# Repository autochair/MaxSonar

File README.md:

# MaxSonar
Board design and code for communication with Maxbotix MaxSonar sensors

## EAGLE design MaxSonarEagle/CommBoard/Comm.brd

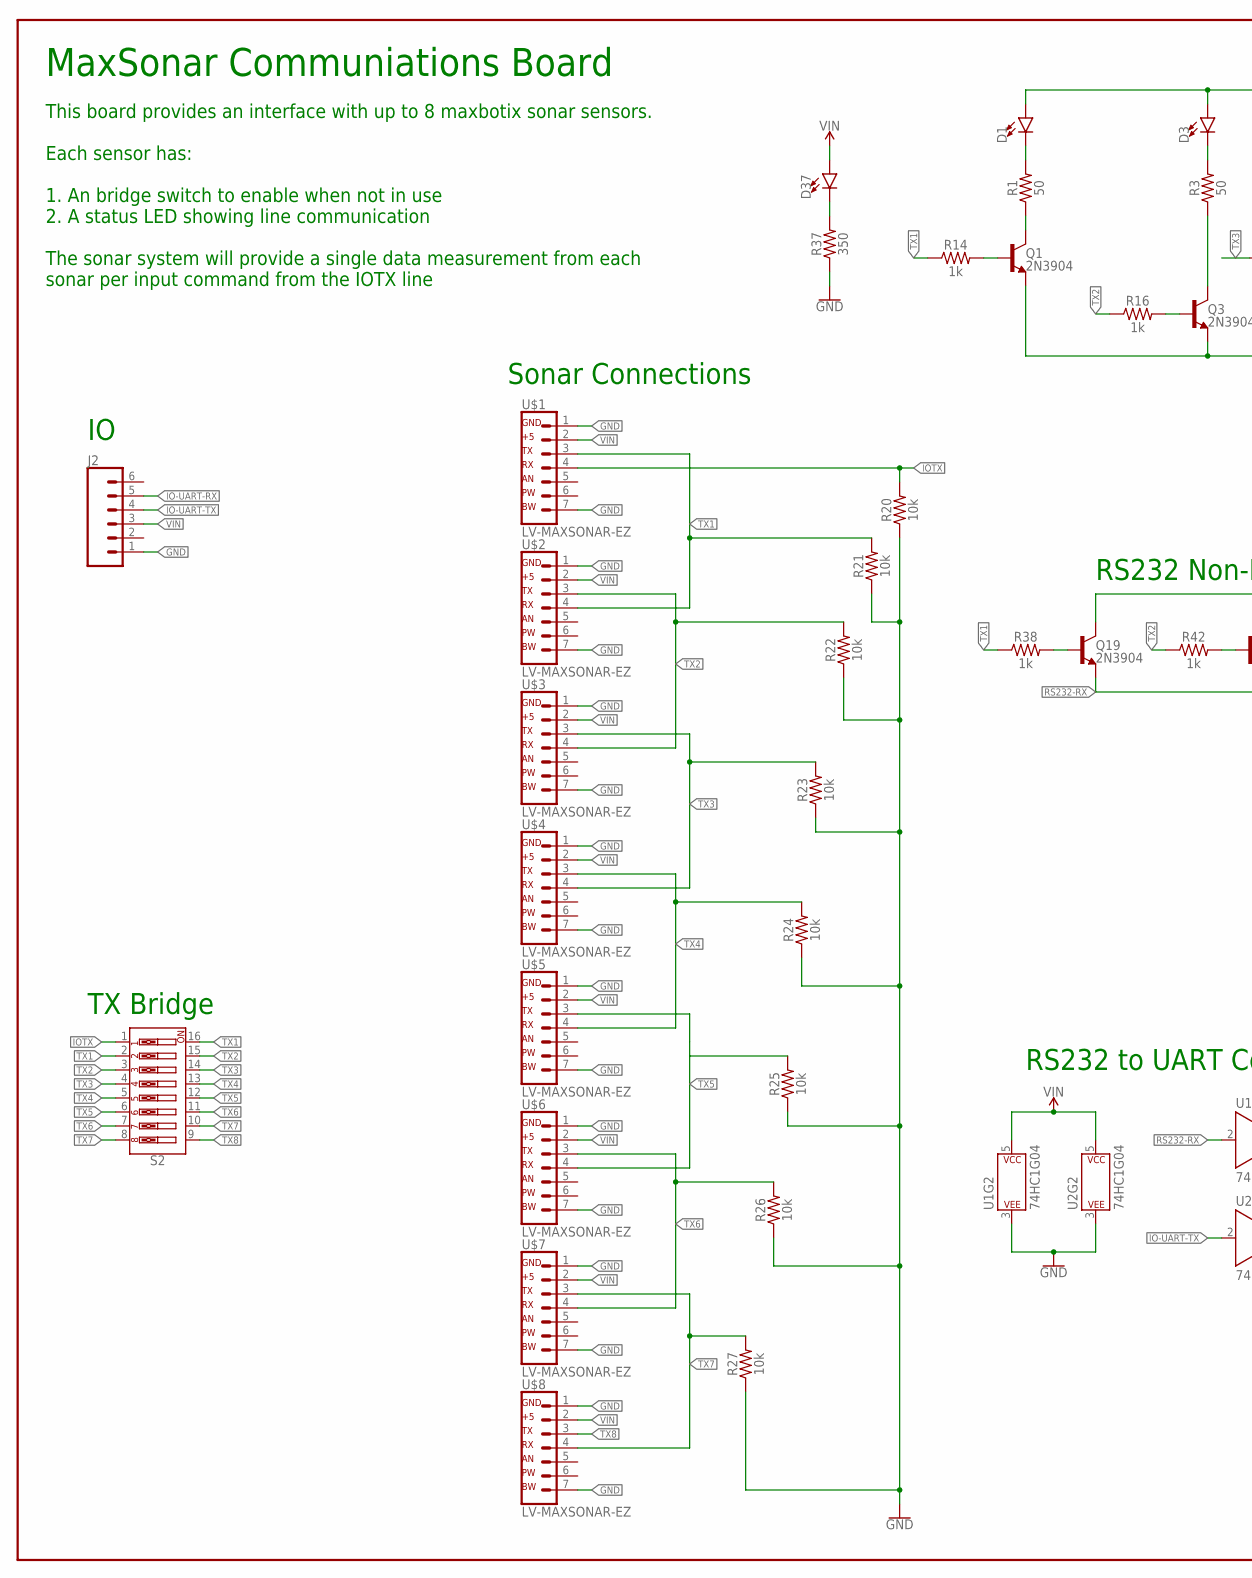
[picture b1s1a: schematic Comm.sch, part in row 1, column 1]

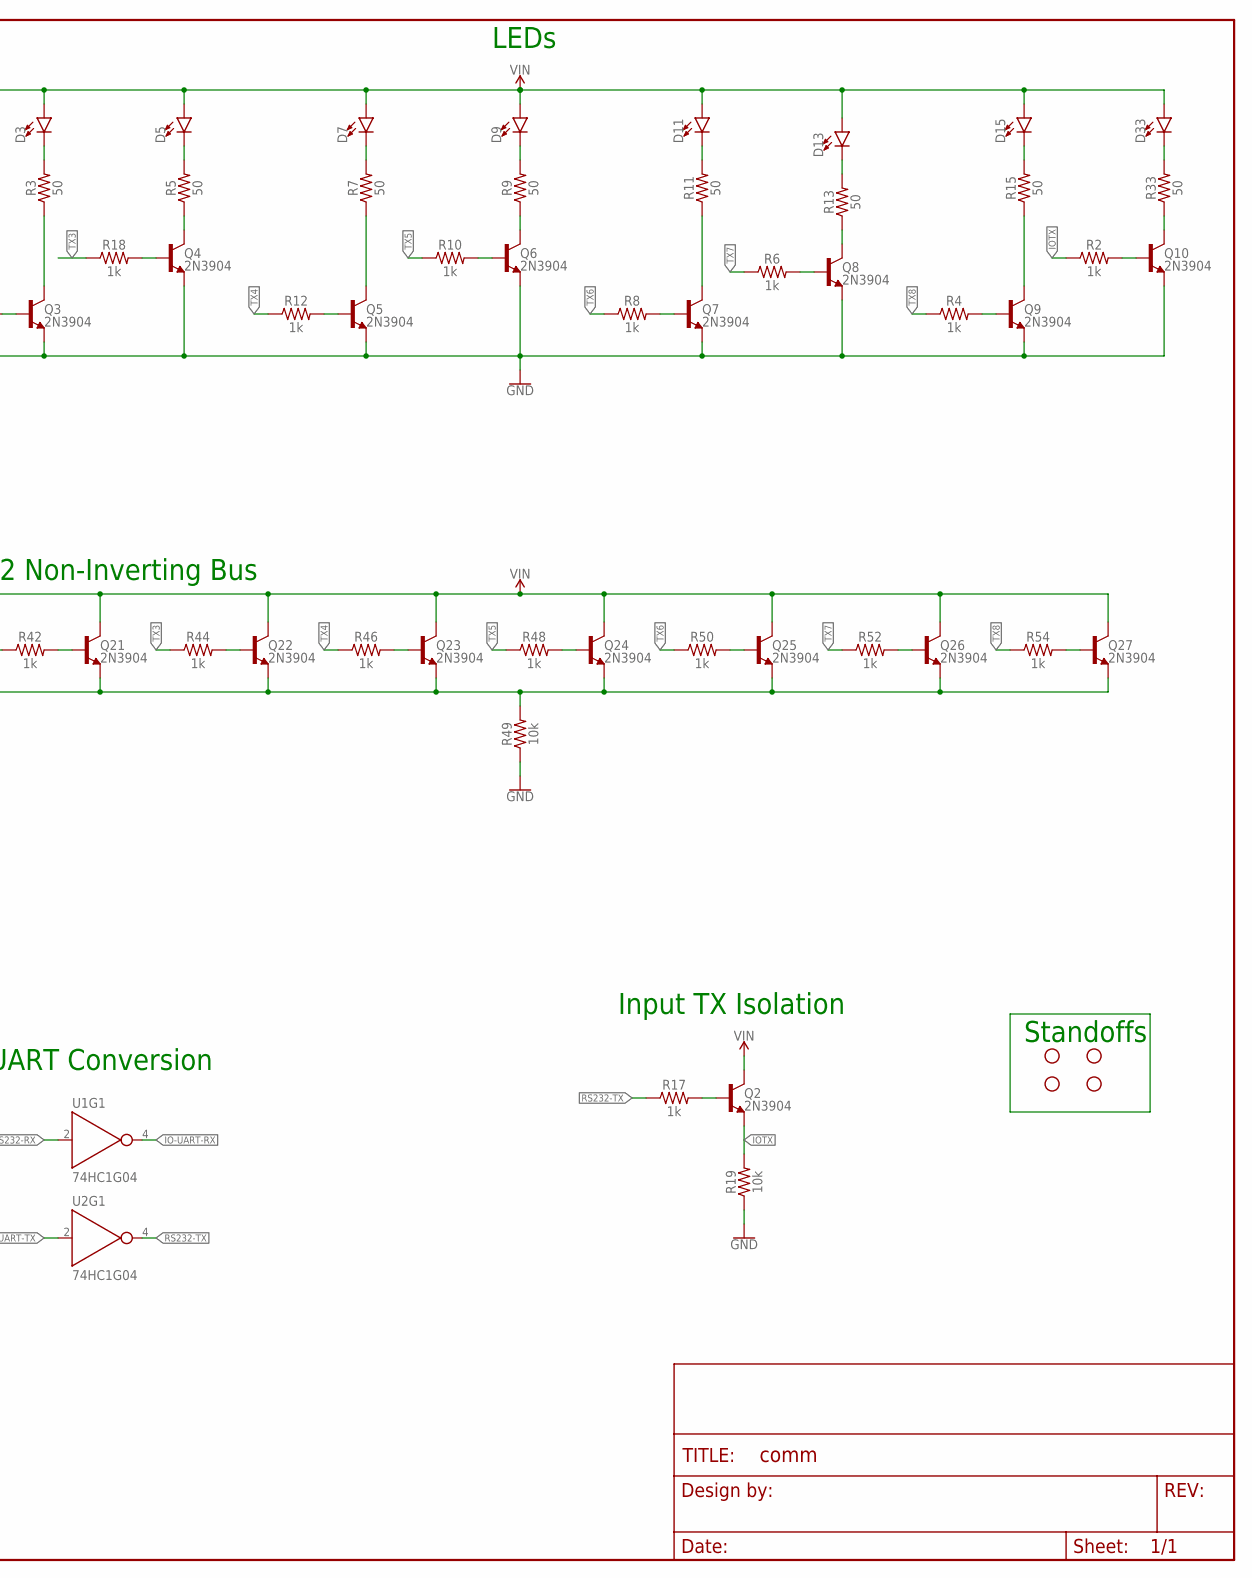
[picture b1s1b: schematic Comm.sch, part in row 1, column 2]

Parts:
D1, D3, D5, D7, D9, D11, D13, D15, D33, D37: LED0603; LED-0603
FRAME1: FRAME-LEDGER; CREATIVE_COMMONS
H1, H2, H3, H4: STAND-OFF
J2: CONN_06POLAR; MOLEX-1X6
Q1, Q2, Q3, Q4, Q5, Q6, Q7, Q8, Q9, Q10, Q19, Q21, Q22, Q23, Q24, Q25, Q26, Q27: 2N3904; SOT23-3
R1, R3, R5, R7, R9, R11, R13, R15, R33: 50; 0805
R2, R4, R6, R8, R10, R12, R14, R16, R17, R18, R38, R42, R44, R46, R48, R50, R52, R54: 1k; 0805
R19, R20, R21, R22, R23, R24, R25, R26, R27, R49: 10k; 0805
R37: 350; 0805
S2: DIP-08-PTH; DIPSWITCH-08
U1, U2: 74HC1G04; SOT353
U$1, U$2, U$3, U$4, U$5, U$6, U$7, U$8: LV-MAXSONAR-EZ; 1X07

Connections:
GND: J2.1, Q1.2 (E), Q3.2 (E), Q4.2 (E), Q5.2 (E), Q6.2 (E), Q7.2 (E), Q8.2 (E), Q9.2 (E), Q10.2 (E), R19.1, R20.1, R21.1, R22.1, R23.1, R24.1, R25.1, R26.1, R27.1, R37.1, R49.1, U1.3 (P$V-), U2.3 (P$V-), U$1.1 (GND), U$1.7 (BW), U$2.1 (GND), U$2.7 (BW), U$3.1 (GND), U$3.7 (BW), U$4.1 (GND), U$4.7 (BW), U$5.1 (GND), U$5.7 (BW), U$6.1 (GND), U$6.7 (BW), U$7.1 (GND), U$7.7 (BW), U$8.1 (GND), U$8.7 (BW)
IO-UART-RX: J2.5, U1.4 (Y)
IO-UART-TX: J2.4, U2.2 (A)
IOTX: Q2.2 (E), R2.1, R19.2, R20.2, S2.1, U$1.4 (RX)
unnamed: D1.C, R1.2
unnamed: Q1.3 (C), R1.1
unnamed: D3.C, R3.2
unnamed: Q3.3 (C), R3.1
unnamed: D5.C, R5.2
unnamed: Q4.3 (C), R5.1
unnamed: D7.C, R7.2
unnamed: Q5.3 (C), R7.1
unnamed: D9.C, R9.2
unnamed: Q6.3 (C), R9.1
unnamed: D11.C, R11.2
unnamed: Q7.3 (C), R11.1
unnamed: D13.C, R13.2
unnamed: Q8.3 (C), R13.1
unnamed: D15.C, R15.2
unnamed: Q9.3 (C), R15.1
unnamed: Q2.1 (B), R17.2
unnamed: Q10.3 (C), R33.1
unnamed: Q10.1 (B), R2.2
unnamed: Q9.1 (B), R4.2
unnamed: Q8.1 (B), R6.2
unnamed: Q7.1 (B), R8.2
unnamed: Q6.1 (B), R10.2
unnamed: Q5.1 (B), R12.2
unnamed: Q1.1 (B), R14.2
unnamed: D33.C, R33.2
unnamed: Q3.1 (B), R16.2
unnamed: D37.C, R37.2
unnamed: Q19.1 (B), R38.2
unnamed: Q21.1 (B), R42.2
unnamed: Q4.1 (B), R18.2
unnamed: Q22.1 (B), R44.2
unnamed: Q23.1 (B), R46.2
unnamed: Q24.1 (B), R48.2
unnamed: Q25.1 (B), R50.2
unnamed: Q26.1 (B), R52.2
unnamed: Q27.1 (B), R54.2
RS232-RX: Q19.2 (E), Q21.2 (E), Q22.2 (E), Q23.2 (E), Q24.2 (E), Q25.2 (E), Q26.2 (E), Q27.2 (E), R49.2, U1.2 (A)
RS232-TX: R17.1, U2.4 (Y)
TX1: R14.1, R21.2, R38.1, S2.2, S2.16, U$1.3 (TX), U$2.4 (RX)
TX2: R16.1, R22.2, R42.1, S2.3, S2.15, U$2.3 (TX), U$3.4 (RX)
TX3: R18.1, R23.2, R44.1, S2.4, S2.14, U$3.3 (TX), U$4.4 (RX)
TX4: R12.1, R24.2, R46.1, S2.5, S2.13, U$4.3 (TX), U$5.4 (RX)
TX5: R10.1, R25.2, R48.1, S2.6, S2.12, U$5.3 (TX), U$6.4 (RX)
TX6: R8.1, R26.2, R50.1, S2.7, S2.11, U$6.3 (TX), U$7.4 (RX)
TX7: R6.1, R27.2, R52.1, S2.8, S2.10, U$7.3 (TX), U$8.4 (RX)
TX8: R4.1, R54.1, S2.9, U$8.3 (TX)
VIN: D1.A, D3.A, D5.A, D7.A, D9.A, D11.A, D13.A, D15.A, D33.A, D37.A, J2.3, Q2.3 (C), Q19.3 (C), Q21.3 (C), Q22.3 (C), Q23.3 (C), Q24.3 (C), Q25.3 (C), Q26.3 (C), Q27.3 (C), U1.5 (P$V+), U2.5 (P$V+), U$1.2 (+5), U$2.2 (+5), U$3.2 (+5), U$4.2 (+5), U$5.2 (+5), U$6.2 (+5), U$7.2 (+5), U$8.2 (+5)

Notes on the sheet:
MaxSonar Communiations Board
This board provides an interface with up to 8 maxbotix sonar sensors. Each sensor has: 1. An bridge switch to enable when not in use 2. A status LED showing line communication The sonar system will provide a single data measurement from each sonar per input command from the IOTX line
LEDs
RS232 Non-Inverting Bus
RS232 to UART Conversion
Sonar Connections
TX Bridge
Input TX Isolation
Standoffs

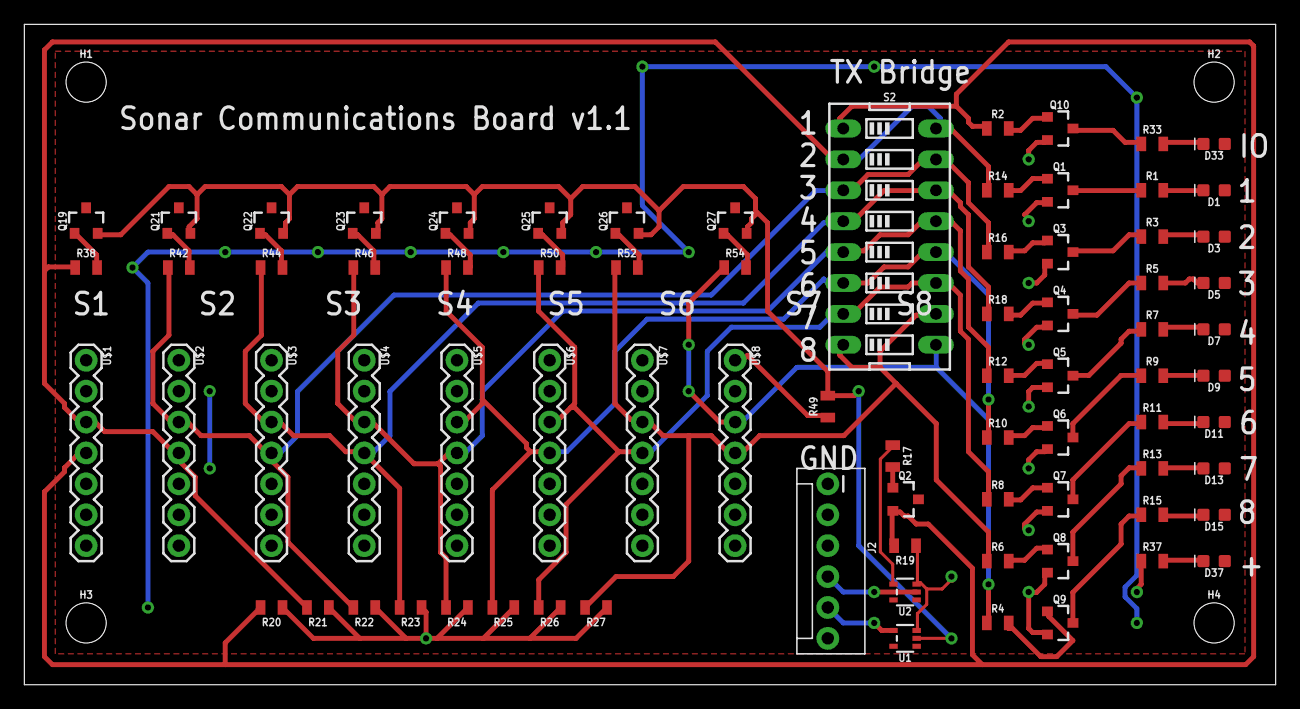
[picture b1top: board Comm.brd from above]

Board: 2 copper layers, 102.8 x 54.3 mm, 83 parts (0 on the bottom side), 52 nets.

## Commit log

2018-04-23 stub for sonar comm board
2018-04-24 added sonar library
2018-04-24 schematic updates
2018-04-26 updated gitignore for eagle
2018-04-26 updated library component
2018-04-26 added design block for led
2018-04-26 finalized board
2018-04-26 generated gerber files
2018-05-10 added pulldown resistors to sonar rx lines

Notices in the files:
parts and their libraries:
SparkFun-LED: Licensing: Creative Commons ShareAlike 4.0 International - https://creativecommons.org/licenses/by-sa/4.0
